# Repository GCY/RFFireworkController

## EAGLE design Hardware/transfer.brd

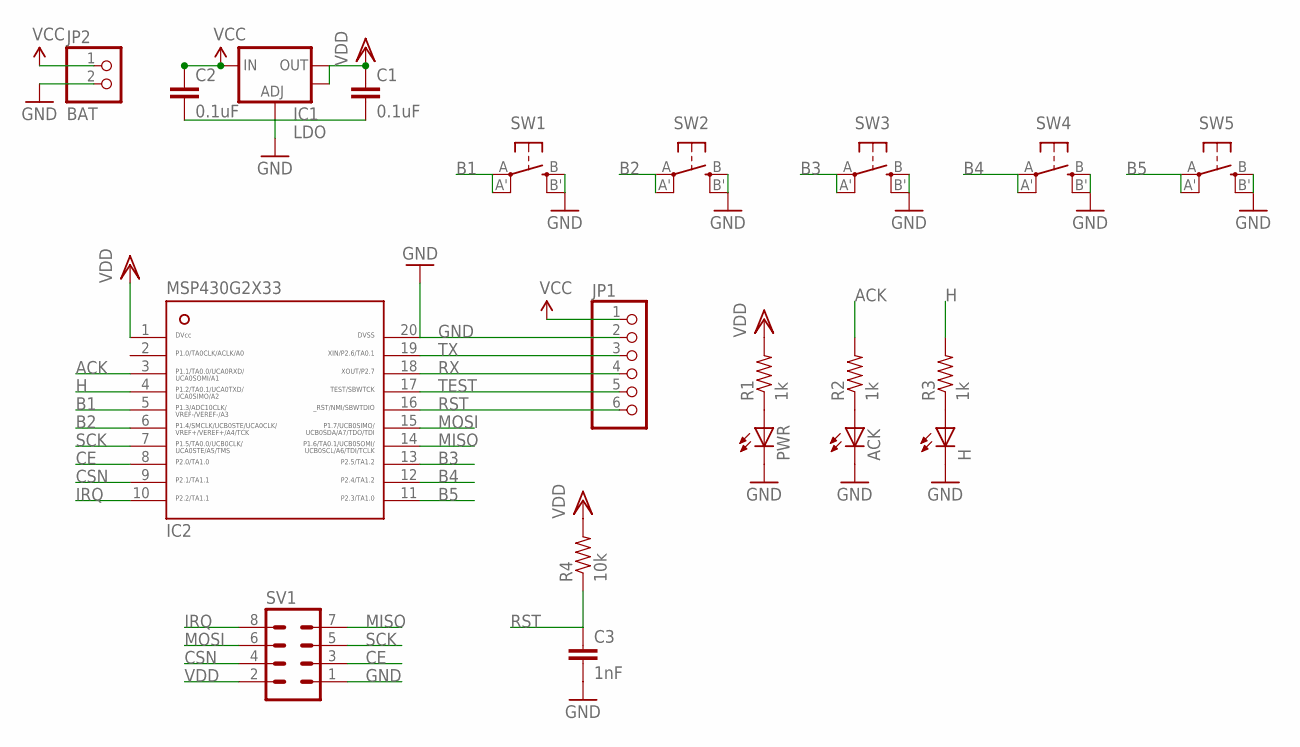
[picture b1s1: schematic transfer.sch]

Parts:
ACK: LEDCHIP-LED0805; CHIP-LED0805
C1, C2: 0.1uF; 0603-CAP
C3: 1nF; 0603-CAP
H: LEDCHIP-LED0805; CHIP-LED0805
IC1: LDO; SOT223
IC2: MSP430; PW20
JP1: PINHD-1X6; 1X06
JP2: BAT; 1X02
PWR: LEDCHIP-LED0805; CHIP-LED0805
R1, R2, R3: 1k; 0805
R4: 10k; 0805
SV1: MA04-2
SW1, SW2, SW3, SW4, SW5: SPST_TACT-EVQQ2; EVQ-Q2

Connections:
ACK: IC2.3, R2.2
B1: IC2.5, SW1.A, SW1.A' (P1)
B2: IC2.6, SW2.A, SW2.A' (P1)
B3: IC2.13, SW3.A, SW3.A' (P1)
B4: IC2.12, SW4.A, SW4.A' (P1)
B5: IC2.11, SW5.A, SW5.A' (P1)
CE: IC2.8, SV1.3
CSN: IC2.9, SV1.4
GND: ACK.C, C1.2, C2.2, C3.2, H.C, IC1.1 (ADJ), IC2.20, JP1.2, JP2.2, PWR.C, SV1.1, SW1.B (S), SW1.B' (S1), SW2.B (S), SW2.B' (S1), SW3.B (S), SW3.B' (S1), SW4.B (S), SW4.B' (S1), SW5.B (S), SW5.B' (S1)
H: IC2.4, R3.2
IRQ: IC2.10, SV1.8
MISO: IC2.14, SV1.7
MOSI: IC2.15, SV1.6
unnamed: PWR.A, R1.1
unnamed: ACK.A, R2.1
unnamed: H.A, R3.1
RST: C3.1, IC2.16, JP1.6, R4.1
RX: IC2.18, JP1.4
SCK: IC2.7, SV1.5
TEST: IC2.17, JP1.5
TX: IC2.19, JP1.3
VCC: C2.1, IC1.3 (IN), JP1.1, JP2.1
VDD: C1.1, IC1.2 (OUT), IC1.4 (OUT), IC2.1, R1.2, R4.2, SV1.2

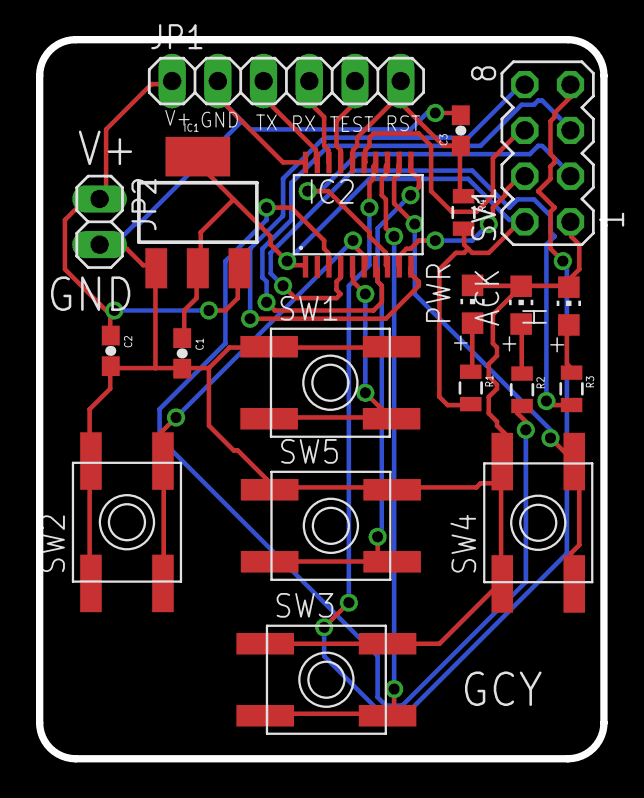
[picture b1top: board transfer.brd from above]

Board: 2 copper layers, 31.3 x 40.0 mm, 20 parts (0 on the bottom side), 23 nets.

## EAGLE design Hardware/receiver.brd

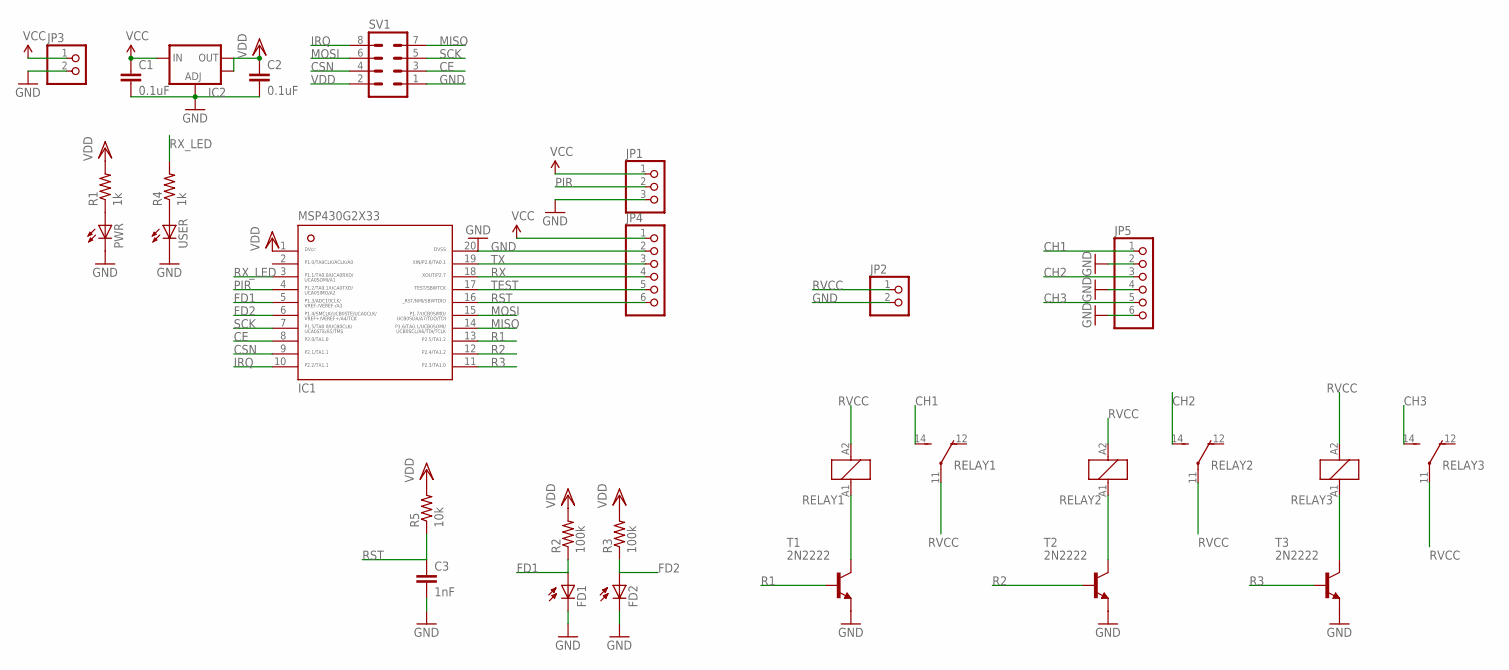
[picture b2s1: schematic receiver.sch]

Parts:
C1, C2: 0.1uF; 0603-CAP
C3: 1nF; 0603-CAP
FD1, FD2: BPX65
IC1: MSP430G2X33-20PW20; PW20
IC2: V_REG_LM1117SOT223; SOT223
JP1: PINHD-1X3; 1X03
JP2, JP3: PINHD-1X2; 1X02
JP4, JP5: PINHD-1X6; 1X06
PWR: LEDCHIP-LED0805; CHIP-LED0805
R1, R4: 1k; 0603
R2, R3: 100k; 0603
R5: 10k; 0603
RELAY1, RELAY2, RELAY3: ZNS5106; ZN5
SV1: MA04-2
T1, T2, T3: 2N2222; TO92-EBC-OVAL
USER: LEDCHIP-LED0805; CHIP-LED0805

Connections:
CE: IC1.8, SV1.3
CH1: JP5.1, RELAY1.14 (S)
CH2: JP5.3, RELAY2.14 (S)
CH3: JP5.5, RELAY3.14 (S)
CSN: IC1.9, SV1.4
FD1: FD1.A, IC1.5, R2.1
FD2: FD2.A, IC1.6, R3.1
GND: C1.2, C2.2, C3.2, FD1.K (C), FD2.K (C), IC1.20, IC2.1 (ADJ), JP1.3, JP2.2, JP3.2, JP4.2, JP5.2, JP5.4, JP5.6, PWR.C, SV1.1, T1.E, T2.E, T3.E, USER.C
IRQ: IC1.10, SV1.8
MISO: IC1.14, SV1.7
MOSI: IC1.15, SV1.6
unnamed: RELAY2.A1 (1), T2.C
unnamed: RELAY3.A1 (1), T3.C
unnamed: PWR.A, R1.1
unnamed: R4.1, USER.A
unnamed: RELAY1.A1 (1), T1.C
PIR: IC1.4, JP1.2
R1: IC1.13, T1.B
R2: IC1.12, T2.B
R3: IC1.11, T3.B
RST: C3.1, IC1.16, JP4.6, R5.1
RVCC: JP2.1, RELAY1.11, RELAY1.A2 (2), RELAY2.11, RELAY2.A2 (2), RELAY3.11, RELAY3.A2 (2)
RX: IC1.18, JP4.4
RX_LED: IC1.3, R4.2
SCK: IC1.7, SV1.5
TEST: IC1.17, JP4.5
TX: IC1.19, JP4.3
VCC: C1.1, IC2.3 (IN), JP1.1, JP3.1, JP4.1
VDD: C2.1, IC1.1, IC2.2 (OUT), IC2.4 (OUT), R1.2, R2.2, R3.2, R5.2, SV1.2

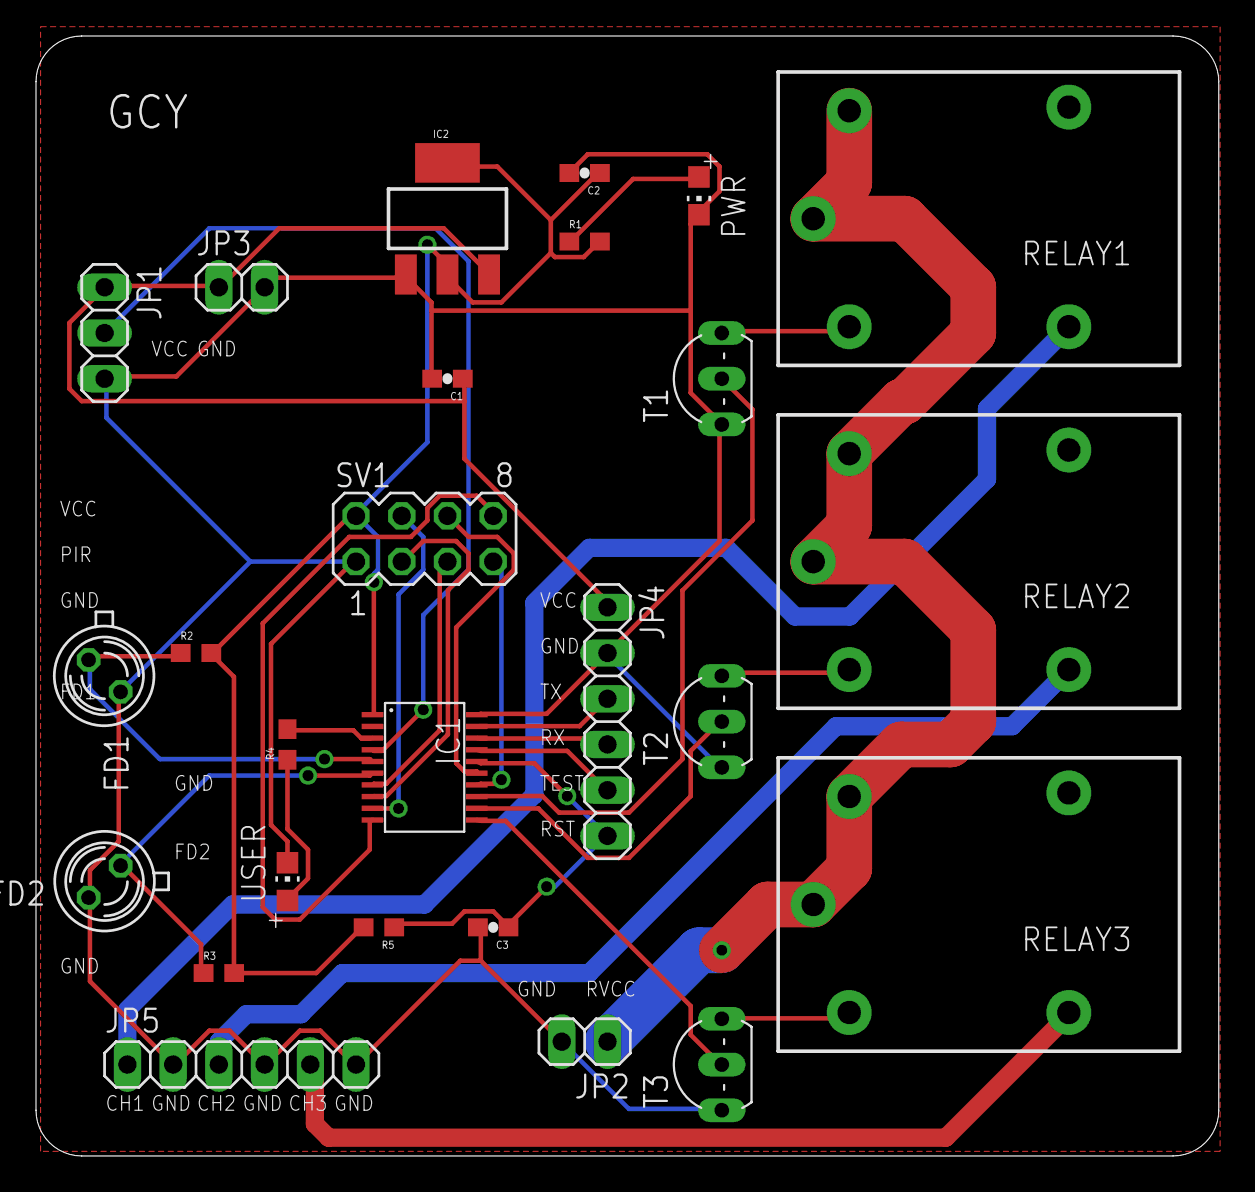
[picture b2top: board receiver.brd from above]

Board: 2 copper layers, 65.7 x 62.2 mm, 26 parts (0 on the bottom side), 29 nets.

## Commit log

2016-09-24 Controller and terminal circuit for Eagle PCB
2016-09-24 Controller and terminal code for Energia MSP430G2443
2016-10-05 add PIR

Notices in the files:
parts and their libraries:
SparkFun-PowerIC: Licensing: CC v3.0 Share-Alike You are welcome to use this library for commercial purposes.
